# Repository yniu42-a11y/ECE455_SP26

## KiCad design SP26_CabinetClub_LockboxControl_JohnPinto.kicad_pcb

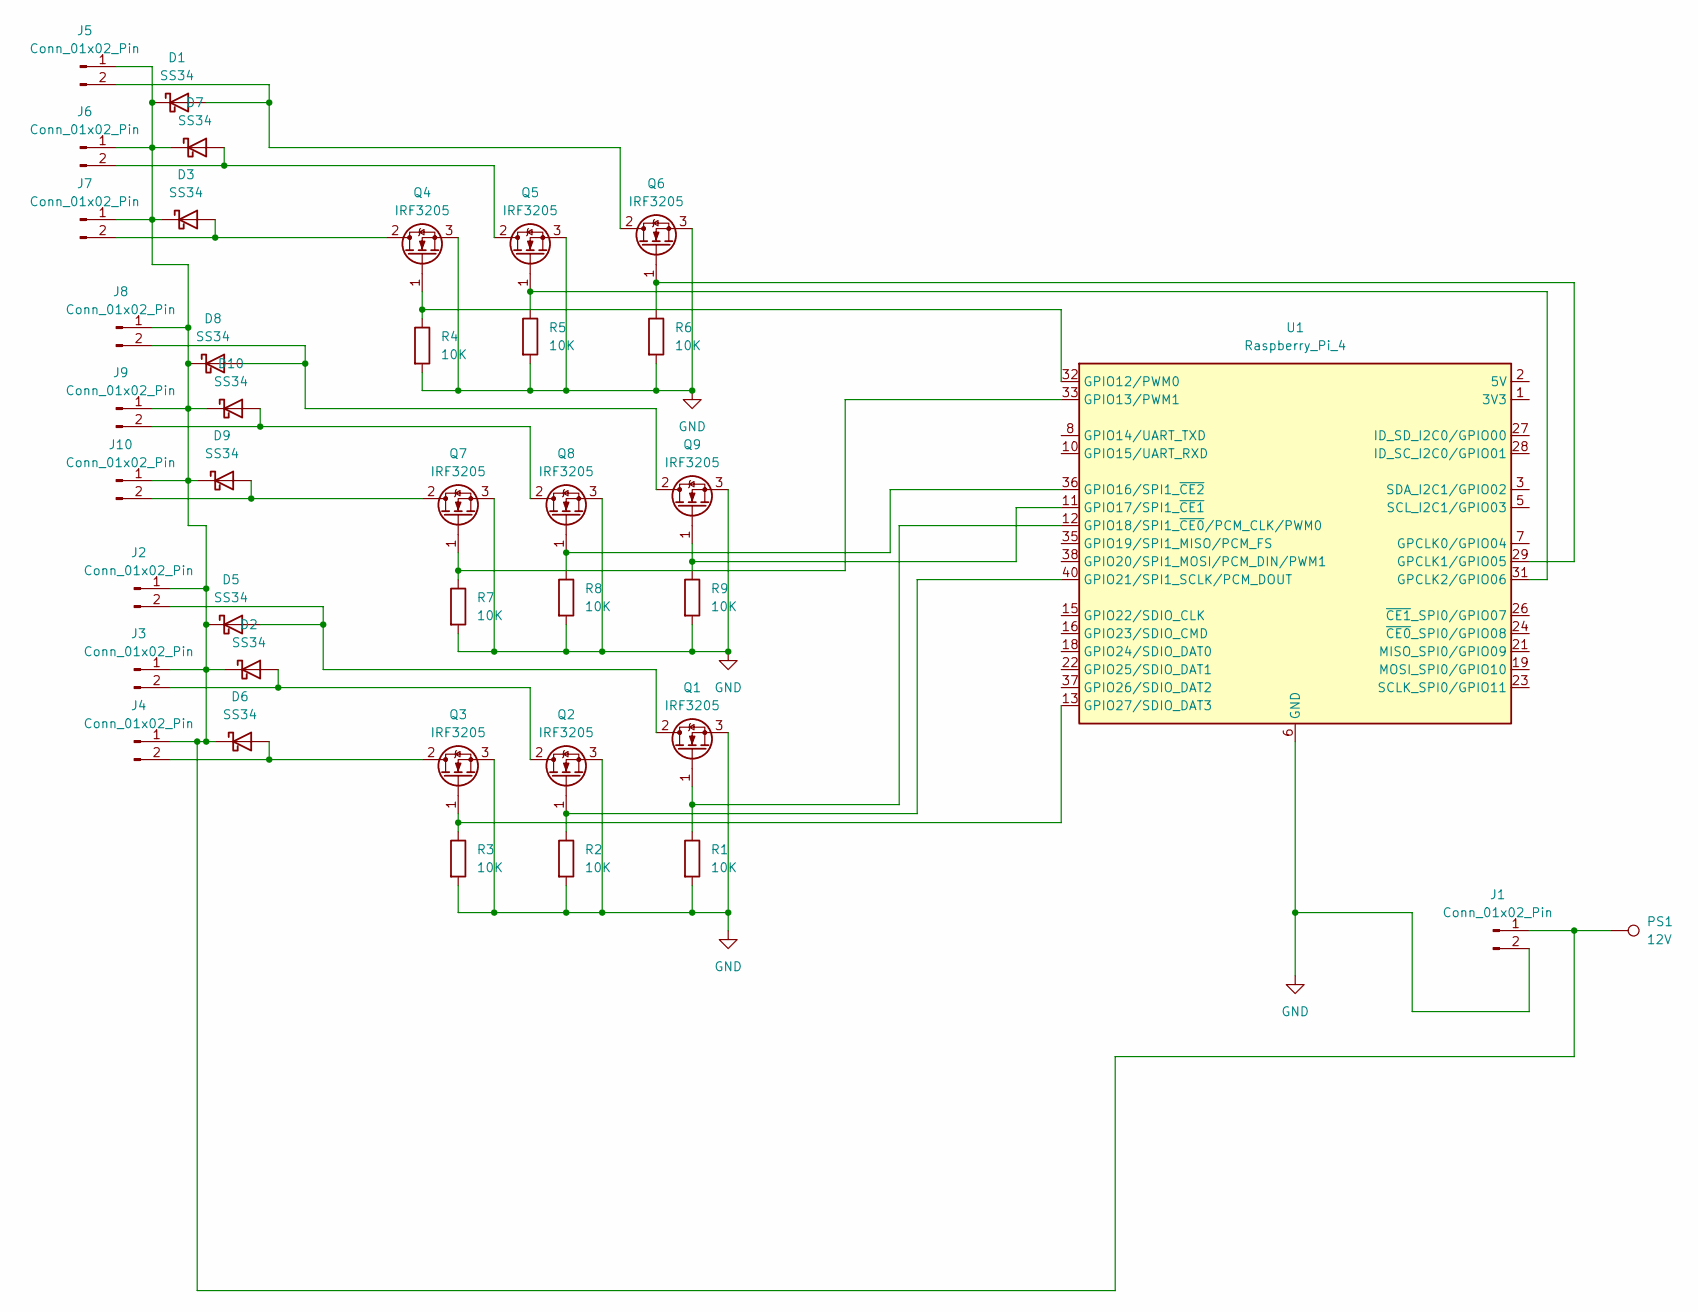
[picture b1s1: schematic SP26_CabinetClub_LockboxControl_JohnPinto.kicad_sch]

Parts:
D1, D2, D3, D5, D6, D7, D8, D9, D10: SS34; D_SMA
J1, J2, J3, J4, J5, J6, J7, J8, J9, J10: Conn_01x02_Pin; JST_EH_B2B-EH-A_1x02_P2.50mm_Vertical
PS1: 12V; TestPoint_Keystone_5000-5004_Miniature
Q1, Q2, Q3, Q4, Q5, Q6, Q7, Q8, Q9: IRF3205; TO-220-3_Vertical
R1, R2, R3, R4, R5, R6, R7, R8, R9: 10K; R_1206_3216Metric_Pad1.30x1.75mm_HandSolder
U1: Raspberry_Pi_4; PinHeader_2x20_P2.54mm_Vertical_SMD

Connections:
GND: J1.2, Q1.3 (S), Q2.3 (S), Q3.3 (S), Q4.3 (S), Q5.3 (S), Q6.3 (S), Q7.3 (S), Q8.3 (S), Q9.3 (S), R1.2, R2.2, R3.2, R4.2, R5.2, R6.2, R7.2, R8.2, R9.2, U1.6 (GND), U1.9 (GND), U1.14 (GND), U1.20 (GND), U1.25 (GND), U1.30 (GND), U1.34 (GND), U1.39 (GND)
unnamed: D1.2 (A), J5.2, Q6.2 (D)
unnamed: D1.1 (K), D2.1 (K), D3.1 (K), D5.1 (K), D6.1 (K), D7.1 (K), D8.1 (K), D9.1 (K), D10.1 (K), J1.1, J2.1, J3.1, J4.1, J5.1, J6.1, J7.1, J8.1, J9.1, J10.1, PS1.1
unnamed: D2.2 (A), J3.2, Q2.2 (D)
unnamed: D3.2 (A), J7.2, Q4.2 (D)
unnamed: D5.2 (A), J2.2, Q1.2 (D)
unnamed: D6.2 (A), J4.2, Q3.2 (D)
unnamed: D7.2 (A), J6.2, Q5.2 (D)
unnamed: D8.2 (A), J8.2, Q9.2 (D)
unnamed: D9.2 (A), J10.2, Q7.2 (D)
unnamed: D10.2 (A), J9.2, Q8.2 (D)
unnamed: Q1.1 (G), R1.1, U1.12 (GPIO18/SPI1_~CE0/PCM_CLK/PWM0)
unnamed: Q2.1 (G), R2.1, U1.40 (GPIO21/SPI1_SCLK/PCM_DOUT)
unnamed: Q3.1 (G), R3.1, U1.13 (GPIO27/SDIO_DAT3)
unnamed: Q4.1 (G), R4.1, U1.32 (GPIO12/PWM0)
unnamed: Q5.1 (G), R5.1, U1.31 (GPCLK2/GPIO06)
unnamed: Q6.1 (G), R6.1, U1.29 (GPCLK1/GPIO05)
unnamed: Q7.1 (G), R7.1, U1.33 (GPIO13/PWM1)
unnamed: Q8.1 (G), R8.1, U1.36 (GPIO16/SPI1_~CE2)
unnamed: Q9.1 (G), R9.1, U1.11 (GPIO17/SPI1_~CE1)
unnamed: U1.1 (3V3), U1.17 (3V3)
unnamed: U1.2 (5V), U1.4 (5V)

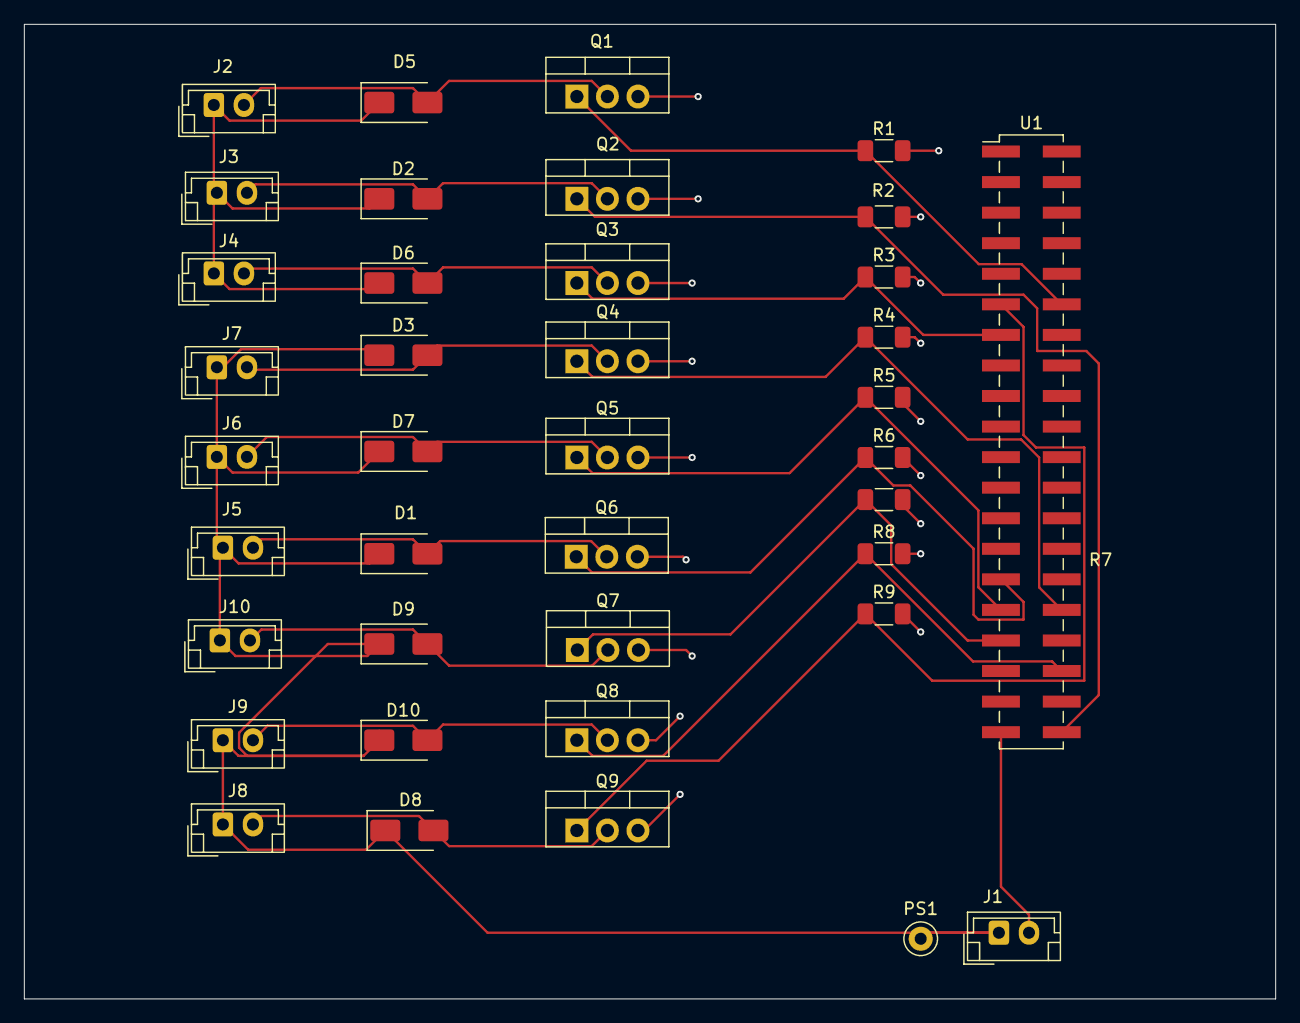
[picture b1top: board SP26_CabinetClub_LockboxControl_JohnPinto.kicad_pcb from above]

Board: 2 copper layers, 104.0 x 81.0 mm, 39 parts (0 on the bottom side), 22 nets.

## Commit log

2026-05-05 Create SP26_CabinetClub_Dispenser_AustinClyne
2026-05-05 Rename Dispenser Rail.SLDPRT to SP26_DispenserRail_CadFile_AustinClyne.SLDPRT
2026-05-05 Rename Sensor Platform.SLDPRT to SP26_Sensor_Platform_CadFile_AustinClyne.SLDPRT
2026-05-05 Rename Spring Mount.SLDPRT to SP26_Spring Mount_CadFile_AustinClyne.SLDPRT
2026-05-05 Rename Ultrasonic sensor.SLDPRT to SP26_Ultrasonic sensor_CadFile_AustinClyne.SLDPRT
2026-05-05 Rename Pusher plate.SLDPRT to SP26_Pusher plate_Cad_File_AustinClyne.SLDPRT
2026-05-05 Rename Dispenser lid.SLDPRT to SP26_Dispenser lid_CadFile_AustinClyne.SLDPRT
2026-05-05 Rename Dispenser base.SLDPRT to SP26_Dispenser base_CadFile_AustinClyne.SLDPRT
2026-05-05 Rename Back Face.SLDPRT to SP26_Back Face_AustinClyne.SLDPRT
2026-05-05 Rename Bottom.SLDPRT to SP_26_LockboxBottom_AustinClyne.SLDPRT
2026-05-05 Rename False base of dispenser.SLDPRT to SP26_False base of dispenser_AustinClyne.SLDPRT
2026-05-05 Rename Front Face.SLDPRT to SP26_Front Face_AustinClyne.SLDPRT
2026-05-05 Rename Wall.SLDPRT to SP26_Lockbox_Wall_AustinClyne.SLDPRT
2026-05-06 Rename Capstone CAD final submission.zip to SP26_Carousel CAD final submission_IanCherkauer.zip
